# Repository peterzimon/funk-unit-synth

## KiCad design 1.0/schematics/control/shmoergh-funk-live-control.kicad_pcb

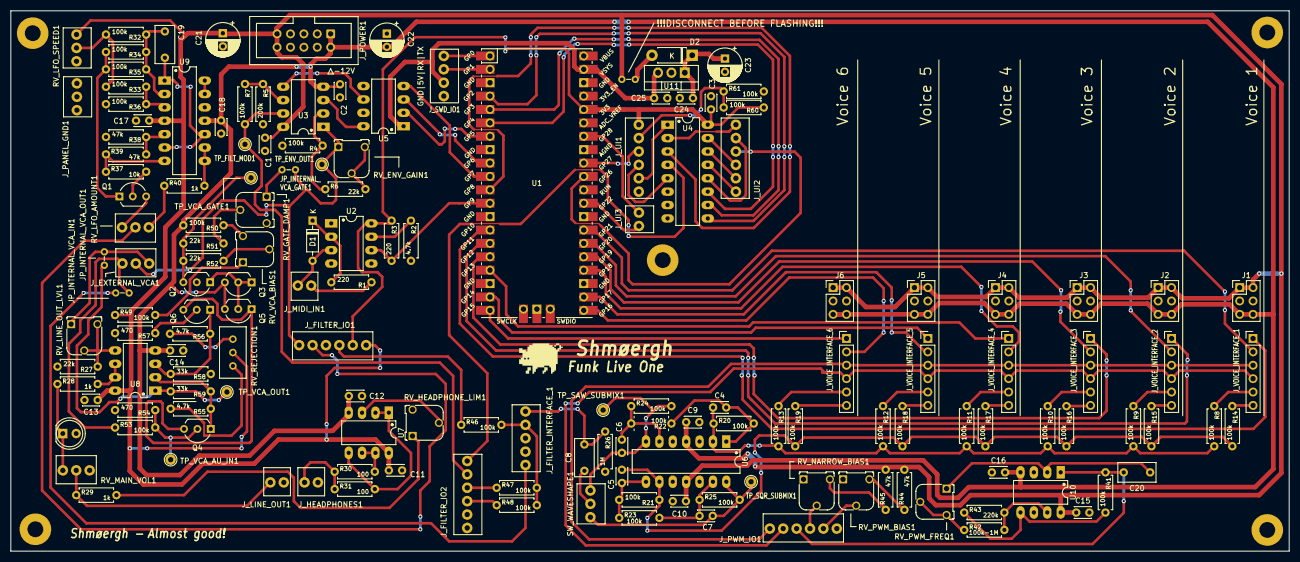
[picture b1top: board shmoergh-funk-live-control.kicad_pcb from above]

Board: 2 copper layers, 242.5 x 102.5 mm, 161 parts (0 on the bottom side), 129 nets.

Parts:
C1, C2, C3, C9, C10, C11, C12, C13, C14, C15, C16, C17, C18, C25: 100n; C_Disc_D3.0mm_W2.0mm_P2.50mm
C4, C5, C6, C7: 22p; C_Disc_D3.0mm_W2.0mm_P2.50mm
C8: 470n (foil); C_Rect_L7.0mm_W3.5mm_P5.00mm
C19: 22n-47n (foil); C_Rect_L7.0mm_W3.5mm_P5.00mm
C20: 470n foil; C_Rect_L7.0mm_W3.5mm_P5.00mm
C21, C22: 100u; CP_Radial_D6.3mm_P2.50mm
C23: 10u; CP_Radial_D6.3mm_P2.50mm
C24: 330n; C_Disc_D3.0mm_W2.0mm_P2.50mm
D1: 1N4148; D_DO-35_SOD27_P7.62mm_Horizontal
D2: 1N4001; D_DO-41_SOD81_P7.62mm_Horizontal
D_NEGATIVE_LIMITER1: Red LED; LED_D5.0mm
H1, H2, H3, H4, H5: MountingHole; MountingHole_3mm_Pad
J1, J2, J3, J4, J5, J6: Power; PinHeader_2x03_P2.54mm_Vertical
JP_INTERNAL_VCA_GATE1: jmpr; Jumper_P2.54mm_D0.7mm
JP_INTERNAL_VCA_IN1: jmpr; Jumper_P2.54mm_D0.7mm
JP_INTERNAL_VCA_OUT1: jmpr; Jumper_P2.54mm_D0.7mm
JP_MCU_EXT_PWR2: jmpr; Jumper_P2.54mm_D0.7mm
J_EXTERNAL_VCA1: Conn_01x03; NSL25_01x03_Vertical
J_FILTER_INTERFACE_1: Conn_01x05; NSL25_01x05_Vertical
J_FILTER_IO1, J_FILTER_IO2: Conn_01x06; NSL25_01x06_Vertical
J_HEADPHONES1: 3.5mm jack; NSL25_01x02_Vertical-AudioJack-TS
J_LINE_OUT1: 3.5mm jack; NSL25_01x02_Vertical-AudioJack-TS
J_MIDI_IN1: Conn_01x02; NSL25_01x02_Vertical
J_PANEL_GND1: Conn_01x03_Pin; NSL25_01x03_Vertical
J_POWER1: Euro Power; IDC-Header_2x05_P2.54mm_Vertical
J_PWM_IO1: Conn_01x06; NSL25_01x06_Vertical
J_SWD_IO1: Conn_01x04; NSL25_01x04_Vertical
J_UI1, J_UI2: Conn_01x06; NSL25_01x06_Vertical
J_UI3: Conn_01x02; NSL25_01x02_Vertical
J_VOICE_INTERFACE_1, J_VOICE_INTERFACE_2, J_VOICE_INTERFACE_3, J_VOICE_INTERFACE_4, J_VOICE_INTERFACE_5, J_VOICE_INTERFACE_6: Conn_01x06; PinHeader_1x06_P2.54mm_Vertical
Q1: BC548C; TO-92_Inline_Wide
Q2: BC558; TO-92_Inline_Wide
Q3, Q4, Q5, Q6: BC548; TO-92_Inline_Wide
R1, R3: 220; R_Axial_DIN0207_L6.3mm_D2.5mm_P7.62mm_Horizontal
R2, R55, R56: 4.7k; R_Axial_DIN0207_L6.3mm_D2.5mm_P7.62mm_Horizontal
R4, R7, R8, R9, R10, R11, R12, R13, R14, R15, R16, R17, R18, R19, R20, R21, R22, R23, R24, R25, R32, R33, R34, R35, R36, R41, R46, R47, R48, R49, R50, R53, R60, R61: 100k; R_Axial_DIN0207_L6.3mm_D2.5mm_P7.62mm_Horizontal
R5: 200k; R_Axial_DIN0207_L6.3mm_D2.5mm_P7.62mm_Horizontal
R6, R27, R51, R52: 22k; R_Axial_DIN0207_L6.3mm_D2.5mm_P7.62mm_Horizontal
R26: 1M; R_Axial_DIN0207_L6.3mm_D2.5mm_P7.62mm_Horizontal
R28, R29, R40: 1k; R_Axial_DIN0207_L6.3mm_D2.5mm_P7.62mm_Horizontal
R30, R31: 100; R_Axial_DIN0207_L6.3mm_D2.5mm_P7.62mm_Horizontal
R37: 10k; R_Axial_DIN0207_L6.3mm_D2.5mm_P7.62mm_Horizontal
R38, R39, R44, R45: 47k; R_Axial_DIN0207_L6.3mm_D2.5mm_P7.62mm_Horizontal
R42: 100k-1M; R_Axial_DIN0207_L6.3mm_D2.5mm_P7.62mm_Horizontal
R43: 220k; R_Axial_DIN0207_L6.3mm_D2.5mm_P7.62mm_Horizontal
R54, R57: 470; R_Axial_DIN0207_L6.3mm_D2.5mm_P7.62mm_Horizontal
R58, R59: 33k; R_Axial_DIN0207_L6.3mm_D2.5mm_P7.62mm_Horizontal
RV_ENV_GAIN1: 200k; Potentiometer_Runtron_RM-065_Vertical
RV_GATE_DAMP1: 100k; Potentiometer_Runtron_RM-065_Vertical
RV_HEADPHONE_LIM1: 10k; Potentiometer_Runtron_RM-065_Vertical
RV_LFO_AMOUNT1: 100k; NSL25_01x03_Vertical
RV_LFO_SPEED1: 100k; NSL25_01x03_Vertical
RV_LINE_OUT_LVL1: 100k; Potentiometer_Runtron_RM-065_Vertical
RV_MAIN_VOL1: A100k; NSL25_01x03_Vertical
RV_NARROW_BIAS1: 100k; Potentiometer_Runtron_RM-065_Vertical
RV_PWM_BIAS1: 100k; Potentiometer_Runtron_RM-065_Vertical
RV_PWM_FREQ1: 1M; Potentiometer_Runtron_RM-065_Vertical
RV_REJECTION1: 10k; Potentiometer_Bourns_3296W_Vertical
RV_VCA_BIAS1: 100k; Potentiometer_Runtron_RM-065_Vertical
SW_WAVESHAPE1: SW_SPDT; NSL25_01x03_Vertical
TP_ENV_OUT1: TestPoint; TestPoint_THTPad_D2.0mm_Drill1.0mm
TP_FILT_MOD1: TestPoint; TestPoint_THTPad_D2.0mm_Drill1.0mm
TP_SAW_SUBMIX1: TestPoint; TestPoint_THTPad_D2.0mm_Drill1.0mm
TP_SQR_SUBMIX1: TestPoint; TestPoint_THTPad_D2.0mm_Drill1.0mm
TP_VCA_AU_IN1: TestPoint; TestPoint_THTPad_D2.0mm_Drill1.0mm
TP_VCA_GATE1: TestPoint; TestPoint_THTPad_D2.0mm_Drill1.0mm
TP_VCA_OUT1: TestPoint; TestPoint_THTPad_D2.0mm_Drill1.0mm
U1: Pico; RPi_Pico_SMD_TH
U2: 6N138; DIP-8_W7.62mm_LongPads
U3, U8, U10: TL072; DIP-8_W7.62mm_LongPads
U4: CD4051B; DIP-16_W7.62mm_LongPads
U5: MCP4822; DIP-8_W7.62mm_LongPads
U6, U9: TL074; DIP-14_W7.62mm_LongPads
U7: NE5532; DIP-8_W7.62mm_LongPads
U11: L7805; TO-220-3_Vertical

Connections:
1.5V: J_UI1.2, R60.2, R61.1
+3.3V: C3.1, J_FILTER_IO1.2, J_UI1.1, R3.1, R60.1, U1.36 (3V3), U2.8 (VCC), U4.16 (VDD)
+5V: C25.1, J_SWD_IO1.3, U1.39 (VSYS), U5.1 (Vdd), U11.3 (OUT)
+12V: C1.1, C9.1, C11.1, C13.1, C15.1, C17.1, C21.1, J1.1, J1.2, J2.1, J2.2, J3.1, J3.2, J4.1, J4.2, J5.1, J5.2, J6.1, J6.2, JP_MCU_EXT_PWR2.1 (A), J_FILTER_IO1.1, J_POWER1.9, J_POWER1.10, R44.2, R45.2, R49.1, RV_LFO_SPEED1.1, RV_REJECTION1.2, U3.8 (V+), U6.4 (V+), U7.8 (V+), U8.8 (V+), U9.4 (V+), U10.8 (V+)
-12V: C2.2, C10.2, C12.2, C14.2, C16.2, C18.2, C22.2, J1.5, J1.6, J2.5, J2.6, J3.5, J3.6, J4.5, J4.6, J5.5, J5.6, J6.5, J6.6, J_POWER1.1, J_POWER1.2, Q3.3 (E), Q5.3 (E), R50.2, U3.4 (V-), U6.11 (V-), U7.4 (V-), U8.4 (V-), U9.11 (V-), U10.4 (V-)
/Digital/AMP_1: J_VOICE_INTERFACE_1.2, U1.27 (GPIO21)
/Digital/AMP_2: J_VOICE_INTERFACE_2.2, U1.26 (GPIO20)
/Digital/AMP_3: J_VOICE_INTERFACE_3.2, U1.25 (GPIO19)
/Digital/AMP_4: J_VOICE_INTERFACE_4.2, U1.24 (GPIO18)
/Digital/AMP_5: J_VOICE_INTERFACE_5.2, U1.22 (GPIO17)
/Digital/AMP_6: J_VOICE_INTERFACE_6.2, U1.21 (GPIO16)
/Digital/Digital UI/DETUNE: J_UI1.5, U4.1 (X4)
/Digital/Digital UI/EXTRA_GPIO1: J_UI3.1, U1.34 (GPIO28_ADC2)
/Digital/Digital UI/EXTRA_GPIO2: J_UI3.2, U1.29 (GPIO22)
/Digital/Digital UI/HOLD: J_UI2.2, U4.14 (X1)
/Digital/Digital UI/KB_TRACKING: J_UI2.6, U4.2 (X6)
/Digital/Digital UI/MODE: J_UI1.3, U1.32 (GPIO27_ADC1)
/Digital/Digital UI/PORTAMENTO: J_UI2.5, U4.12 (X3)
/Digital/Digital UI/RING: J_UI2.3, U4.15 (X2)
/Digital/Digital UI/RING_TIME: J_UI2.4, U1.31 (GPIO26_ADC0)
/Digital/Digital UI/SOFT: J_UI2.1, U4.13 (X0)
/Digital/Digital UI/SOLO_CHORD: J_UI1.4, U4.5 (X5)
/Digital/ENVELOPE: JP_INTERNAL_VCA_GATE1.2 (B), J_EXTERNAL_VCA1.2, J_FILTER_IO1.6, RV_ENV_GAIN1.1, TP_ENV_OUT1.1, U3.1
/Digital/FILTER_MOD: J_FILTER_IO2.2, R7.2, TP_FILT_MOD1.1, U3.7
/Digital/RESET_1: J_VOICE_INTERFACE_1.1, U1.14 (GPIO10)
/Digital/RESET_2: J_VOICE_INTERFACE_2.1, U1.15 (GPIO11)
/Digital/RESET_3: J_VOICE_INTERFACE_3.1, U1.16 (GPIO12)
/Digital/RESET_4: J_VOICE_INTERFACE_4.1, U1.17 (GPIO13)
/Digital/RESET_5: J_VOICE_INTERFACE_5.1, U1.19 (GPIO14)
/Digital/RESET_6: J_VOICE_INTERFACE_6.1, U1.20 (GPIO15)
/Digital/WAH_VELOCITY: J_FILTER_IO2.1, U4.4 (X7)
/Filter Interface/AUDIO_IN: C8.2, J_FILTER_INTERFACE_1.1, R26.1
/Filter Interface/AUDIO_OUT: JP_INTERNAL_VCA_IN1.2 (B), J_FILTER_INTERFACE_1.5
/Filter Interface/LFO_IN: J_FILTER_IO1.5, RV_LFO_AMOUNT1.2
/LFO + PWM/PULSE_WIDTH: J_PWM_IO1.1, J_VOICE_INTERFACE_1.3, J_VOICE_INTERFACE_2.3, J_VOICE_INTERFACE_3.3, J_VOICE_INTERFACE_4.3, J_VOICE_INTERFACE_5.3, J_VOICE_INTERFACE_6.3
/LFO + PWM/PWM_OUT: J_PWM_IO1.2, J_VOICE_INTERFACE_1.4, J_VOICE_INTERFACE_2.4, J_VOICE_INTERFACE_3.4, J_VOICE_INTERFACE_4.4, J_VOICE_INTERFACE_5.4, J_VOICE_INTERFACE_6.4
/Mixer/SAW_1_IN: J_VOICE_INTERFACE_1.5, R8.1
/Mixer/SAW_2_IN: J_VOICE_INTERFACE_2.5, R9.1
/Mixer/SAW_3_IN: J_VOICE_INTERFACE_3.5, R10.1
/Mixer/SAW_4_IN: J_VOICE_INTERFACE_4.5, R11.1
/Mixer/SAW_5_IN: J_VOICE_INTERFACE_5.5, R12.1
/Mixer/SAW_6_IN: J_VOICE_INTERFACE_6.5, R13.1
/Mixer/SQR_1_IN: J_VOICE_INTERFACE_1.6, R14.1
/Mixer/SQR_2_IN: J_VOICE_INTERFACE_2.6, R15.1
/Mixer/SQR_3_IN: J_VOICE_INTERFACE_3.6, R16.1
/Mixer/SQR_4_IN: J_VOICE_INTERFACE_4.6, R17.1
/Mixer/SQR_5_IN: J_VOICE_INTERFACE_5.6, R18.1
/Mixer/SQR_6_IN: J_VOICE_INTERFACE_6.6, R19.1
/Output/AUDIO_IN: JP_INTERNAL_VCA_OUT1.2 (B), J_EXTERNAL_VCA1.3, RV_LINE_OUT_LVL1.1
/VCA (Internal)/AUDIO_IN: JP_INTERNAL_VCA_IN1.1 (A), J_EXTERNAL_VCA1.1, R53.1
/VCA (Internal)/AUDIO_OUT: JP_INTERNAL_VCA_OUT1.1 (A), R59.2, TP_VCA_OUT1.1, U8.1
/VCA (Internal)/GATE: JP_INTERNAL_VCA_GATE1.1 (A), RV_GATE_DAMP1.1
CUTOFF_IN: J_FILTER_IO1.3, R46.1
DAC_CS: U1.7 (GPIO5), U5.2 (~CS)
DAC_SCK: U1.9 (GPIO6), U5.3 (SCK)
DAC_SDI: U1.10 (GPIO7), U5.4 (SDI)
FILTER_DIGI_MOD_IN: J_FILTER_IO2.3, R47.1
GND: C1.2, C2.1, C3.2, C9.2, C10.1, C11.2, C12.1, C13.2, C14.1, C15.2, C16.1, C17.2, C18.1, C21.2, C22.1, C23.2, C24.2, C25.2, D_NEGATIVE_LIMITER1.2 (A), J1.3, J1.4, J2.3, J2.4, J3.3, J3.4, J4.3, J4.4, J5.3, J5.4, J6.3, J6.4, J_FILTER_IO2.5, J_FILTER_IO2.6, J_HEADPHONES1.S, J_LINE_OUT1.S, J_PANEL_GND1.1, J_PANEL_GND1.2, J_PANEL_GND1.3, J_POWER1.3, J_POWER1.4, J_POWER1.5, J_POWER1.6, J_POWER1.7, J_POWER1.8, J_PWM_IO1.6, J_SWD_IO1.4, J_UI1.6, Q1.3 (E), Q2.2 (B), R2.2, R4.2, R5.2, R26.2, R27.2, R36.2, R38.2, R54.2, R57.2, R58.1, R61.2, RV_GATE_DAMP1.3, RV_HEADPHONE_LIM1.3, RV_LFO_AMOUNT1.3, RV_LFO_SPEED1.3, RV_MAIN_VOL1.3, RV_NARROW_BIAS1.1, RV_PWM_BIAS1.1, U1.3 (GND), U1.8 (GND), U1.13 (GND), U1.18 (GND), U1.23 (GND), U1.28 (GND), U1.38 (GND), U2.5 (GND), U4.6 (INH), U4.7 (VEE), U4.8 (VSS), U5.5 (~LDAC), U5.7 (Vss), U6.3 (+), U6.5 (+), U6.10 (+), U6.12 (+), U9.12 (+), U10.3 (+), U10.6 (-), U11.2 (GND)
MIDI_IN: R3.2, U1.12 (GPIO9), U2.6 (VO2)
MUX_A: U1.6 (GPIO4), U4.11 (A)
MUX_B: U1.5 (GPIO3), U4.10 (B)
MUX_BINARY: U1.11 (GPIO8), U4.3 (X)
MUX_C: U1.4 (GPIO2), U4.9 (C)
unnamed: C4.2, R20.2, R22.1, U6.1
unnamed: C5.2, R21.2, R23.1, U6.8
unnamed: D1.2 (A), J_MIDI_IN1.2, U2.3 (C2)
unnamed: D1.1 (K), R1.2, U2.2 (C1)
unnamed: D2.2 (A), JP_MCU_EXT_PWR2.2 (B)
unnamed: C23.1, C24.1, D2.1 (K), U11.1 (IN)
unnamed: D_NEGATIVE_LIMITER1.1 (K), R28.1, RV_MAIN_VOL1.1
unnamed: J_FILTER_INTERFACE_1.2, R46.2, R47.2, R48.2
unnamed: J_HEADPHONES1.T, R30.1, R31.1
unnamed: J_LINE_OUT1.T, R29.1, RV_MAIN_VOL1.2
unnamed: J_MIDI_IN1.1, R1.1
unnamed: Q1.2 (B), R37.2
unnamed: Q1.1 (C), R34.2, R35.2
unnamed: Q2.1 (C), Q3.1 (C), Q3.2 (B), Q5.2 (B)
unnamed: Q2.3 (E), R51.2, R52.2, TP_VCA_GATE1.1
unnamed: Q4.2 (B), R53.2, R54.1, TP_VCA_AU_IN1.1
unnamed: Q4.1 (C), R55.1, R59.1, U8.2 (-)
unnamed: Q4.3 (E), Q5.1 (C), Q6.3 (E)
unnamed: Q6.2 (B), R57.1
unnamed: Q6.1 (C), R56.1, R58.2, U8.3 (+)
unnamed: R6.2, RV_ENV_GAIN1.2, RV_ENV_GAIN1.3
unnamed: R29.2, RV_HEADPHONE_LIM1.1
unnamed: R32.2, R33.2, RV_LFO_SPEED1.2
unnamed: R37.1, R39.1, U9.7
unnamed: R40.1, RV_LFO_AMOUNT1.1
unnamed: R42.1, RV_PWM_FREQ1.2, RV_PWM_FREQ1.3
unnamed: R42.2, R43.2, U10.7
unnamed: R44.1, RV_PWM_BIAS1.3
unnamed: R45.1, RV_NARROW_BIAS1.3
unnamed: R49.2, RV_VCA_BIAS1.1
unnamed: R50.1, RV_VCA_BIAS1.3
unnamed: R51.1, RV_GATE_DAMP1.2
unnamed: R52.1, RV_VCA_BIAS1.2
unnamed: R55.2, RV_REJECTION1.1
unnamed: R56.2, RV_REJECTION1.3
unnamed: C6.2, R24.2, SW_WAVESHAPE1.1 (A), TP_SAW_SUBMIX1.1, U6.7
unnamed: C8.1, SW_WAVESHAPE1.2 (B)
unnamed: C7.2, R25.2, SW_WAVESHAPE1.3 (C), TP_SQR_SUBMIX1.1, U6.14
unnamed: R2.1, U2.7 (VO1)
unnamed: U3.3 (+), U5.8 (VA)
unnamed: R4.1, R6.1, U3.2 (-)
unnamed: U3.5 (+), U5.6 (VB)
unnamed: R5.1, R7.1, U3.6 (-)
unnamed: C4.1, R8.2, R9.2, R10.2, R11.2, R12.2, R13.2, R20.1, U6.2 (-)
unnamed: C6.1, R22.2, R24.1, U6.6 (-)
unnamed: C5.1, R14.2, R15.2, R16.2, R17.2, R18.2, R19.2, R21.1, U6.9 (-)
unnamed: C7.1, R23.2, R25.1, U6.13 (-)
unnamed: RV_HEADPHONE_LIM1.2, U7.3 (+)
unnamed: R31.2, U7.1, U7.2 (-), U7.5 (+)
unnamed: R30.2, U7.6 (-), U7.7
unnamed: R27.1, RV_LINE_OUT_LVL1.2, RV_LINE_OUT_LVL1.3, U8.5 (+)
unnamed: R28.2, U8.6 (-), U8.7
unnamed: R33.1, R36.1, U9.3 (+)
unnamed: C19.2, R32.1, R34.1, R35.1, U9.2 (-)
unnamed: R38.1, R39.2, U9.5 (+)
unnamed: C19.1, U9.1, U9.6 (-), U9.10 (+)
unnamed: R40.2, U9.8, U9.9 (-)
unnamed: U9.13 (-), U9.14
unnamed: C20.1, RV_PWM_FREQ1.1, U10.2 (-)
unnamed: R41.2, R43.1, U10.5 (+)
PWM_LFO: C20.2, J_PWM_IO1.3, R41.1, U10.1
PWM_LFO_BIAS: J_PWM_IO1.5, RV_PWM_BIAS1.2
PWM_NARROW_BIAS: J_PWM_IO1.4, RV_NARROW_BIAS1.2
UART_RX: J_SWD_IO1.2, U1.2 (GPIO1)
UART_TX: J_SWD_IO1.1, U1.1 (GPIO0)
WAH_AMNT_IN: J_FILTER_IO2.4, R48.1

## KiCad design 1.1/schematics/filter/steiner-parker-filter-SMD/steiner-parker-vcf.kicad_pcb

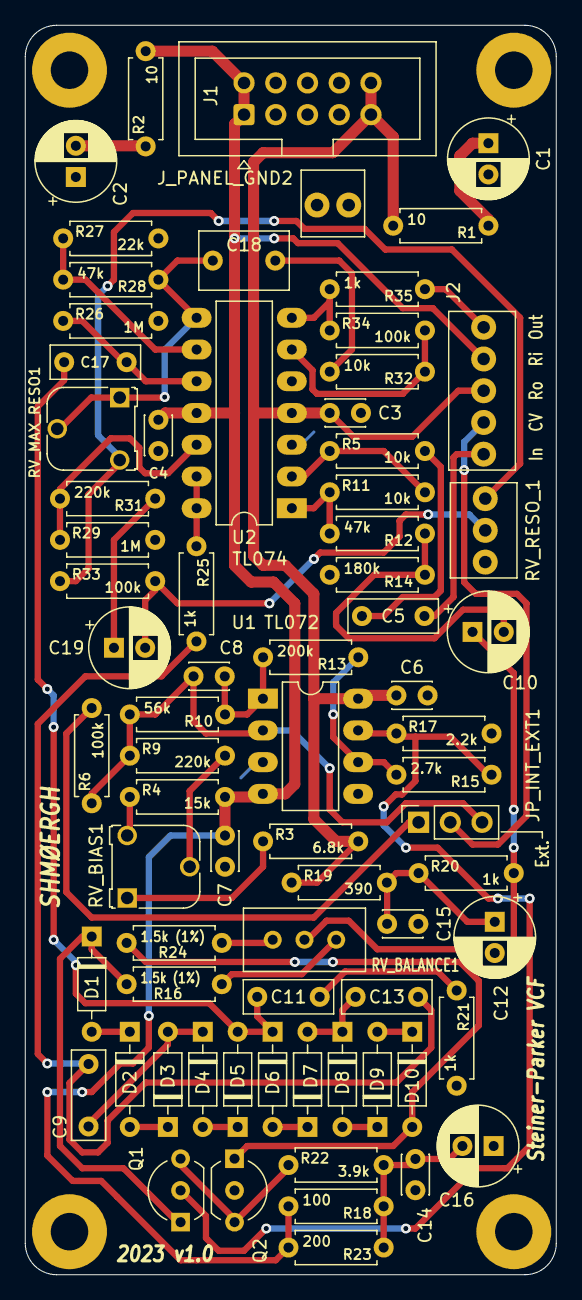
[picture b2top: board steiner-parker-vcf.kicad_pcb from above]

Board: 2 copper layers, 42.5 x 100.0 mm, 77 parts (0 on the bottom side), 50 nets.

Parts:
C1, C2, C12, C16: 100u; CP_Radial_D6.3mm_P2.50mm
C3, C4, C6, C7, C14, C15: 100n; C_Disc_D3.0mm_W2.0mm_P2.50mm
C5: 470n (Foil); C_Rect_L7.0mm_W2.5mm_P5.00mm
C8: 10n; C_Disc_D3.0mm_W2.0mm_P2.50mm
C9, C11, C13: 1n (Foil); C_Rect_L7.0mm_W2.5mm_P5.00mm
C10: 2.2u; CP_Radial_D6.3mm_P2.50mm
C17: 470n (foil); C_Rect_L7.0mm_W2.5mm_P5.00mm
C18: 1u (Foil); C_Rect_L7.0mm_W4.5mm_P5.00mm
C19: 10u; CP_Radial_D6.3mm_P2.50mm
D1, D2, D3, D4, D5, D6, D7, D8, D9, D10: 1N4148; D_DO-35_SOD27_P7.62mm_Horizontal
H1, H2, H3, H4: MountingHole; MountingHole_3mm_Pad
J1: Eurorack Power; IDC-Header_2x05_P2.54mm_Vertical
J2: Conn_01x05_Male; NSL25_01x05_Vertical
JP_INT_EXT1: Internal/External CV; PinSocket_1x03_P2.54mm_Vertical
J_PANEL_GND2: Panel ground; NSL25_01x02_Vertical
Q1, Q2: BC547B; TO-92_Inline_Wide
R1, R2: 10; R_Axial_DIN0207_L6.3mm_D2.5mm_P7.62mm_Horizontal
R3: 6.8k; R_Axial_DIN0207_L6.3mm_D2.5mm_P7.62mm_Horizontal
R4: 15k; R_Axial_DIN0207_L6.3mm_D2.5mm_P7.62mm_Horizontal
R5, R11, R32: 10k; R_Axial_DIN0207_L6.3mm_D2.5mm_P7.62mm_Horizontal
R6, R33, R34: 100k; R_Axial_DIN0207_L6.3mm_D2.5mm_P7.62mm_Horizontal
R9, R31: 220k; R_Axial_DIN0207_L6.3mm_D2.5mm_P7.62mm_Horizontal
R10: 56k; R_Axial_DIN0207_L6.3mm_D2.5mm_P7.62mm_Horizontal
R12, R28: 47k; R_Axial_DIN0207_L6.3mm_D2.5mm_P7.62mm_Horizontal
R13: 200k; R_Axial_DIN0207_L6.3mm_D2.5mm_P7.62mm_Horizontal
R14: 180k; R_Axial_DIN0207_L6.3mm_D2.5mm_P7.62mm_Horizontal
R15: 2.7k; R_Axial_DIN0207_L6.3mm_D2.5mm_P7.62mm_Horizontal
R16, R24: 1.5k (1%); R_Axial_DIN0207_L6.3mm_D2.5mm_P7.62mm_Horizontal
R17: 2.2k; R_Axial_DIN0207_L6.3mm_D2.5mm_P7.62mm_Horizontal
R18: 100; R_Axial_DIN0207_L6.3mm_D2.5mm_P7.62mm_Horizontal
R19: 390; R_Axial_DIN0207_L6.3mm_D2.5mm_P7.62mm_Horizontal
R20, R21, R25, R35: 1k; R_Axial_DIN0207_L6.3mm_D2.5mm_P7.62mm_Horizontal
R22: 3.9k; R_Axial_DIN0207_L6.3mm_D2.5mm_P7.62mm_Horizontal
R23: 200; R_Axial_DIN0207_L6.3mm_D2.5mm_P7.62mm_Horizontal
R26, R29: 1M; R_Axial_DIN0207_L6.3mm_D2.5mm_P7.62mm_Horizontal
R27: 22k; R_Axial_DIN0207_L6.3mm_D2.5mm_P7.62mm_Horizontal
RV_BALANCE1: 1k (precision); Potentiometer_Bourns_3296W_Vertical
RV_BIAS1: 10k; Potentiometer_Runtron_RM-065_Vertical
RV_MAX_RESO1: 100k; Potentiometer_Runtron_RM-065_Vertical
RV_RESO_1: 100k; NSL25_01x03_Vertical
U1: TL072; DIP-8_W7.62mm_LongPads
U2: TL074; DIP-14_W7.62mm_LongPads

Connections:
+12V: C3.1, C6.1, J1.9, J1.10, J2.3, R1.2, R3.2, R19.1, U1.8 (V+), U2.4 (V+)
-12V: C4.2, C7.2, J1.1, J1.2, J2.4, R2.2, R4.2, R18.2, R23.2, U1.4 (V-), U2.11 (V-)
AUDIO_IN: C5.2, J2.1
CV: J2.2, JP_INT_EXT1.2 (C)
GND: C1.2, C2.1, C3.2, C4.1, C6.2, C7.1, C12.2, C14.2, C15.2, C16.1, J1.3, J1.4, J1.5, J1.6, J1.7, J1.8, J_PANEL_GND2.1, J_PANEL_GND2.2, Q2.2 (B), R14.2, R17.2, R21.2, R26.2, R27.2, R29.2, RV_RESO_1.1, U1.3 (+), U1.5 (+), U2.3 (+), U2.5 (+)
unnamed: C1.1, R1.1
unnamed: C2.2, R2.1
unnamed: C5.1, R5.2
unnamed: C8.1, R10.1, R13.2, U1.1
unnamed: C10.1, R20.2, RV_BALANCE1.2
unnamed: C10.2, R12.1, R14.1
unnamed: C11.2, R21.1
unnamed: C12.1, C15.1, R19.2, R20.1
unnamed: C9.2, C13.2, R25.2
unnamed: C14.1, C16.2, R18.1, R22.2, R23.1
unnamed: C18.1, R32.2
unnamed: C18.2, R28.1, RV_MAX_RESO1.1, RV_MAX_RESO1.2, U2.8
unnamed: C19.1, R31.1
unnamed: C19.2, R33.2, RV_RESO_1.2
unnamed: D1.2 (A), D2.1 (K)
unnamed: D1.1 (K), Q1.1 (C), R16.2
unnamed: D2.2 (A), D3.1 (K)
unnamed: C9.1, D3.2 (A), D4.1 (K)
unnamed: D4.2 (A), D5.1 (K)
unnamed: C11.1, C17.2, D5.2 (A), D6.1 (K)
unnamed: D6.2 (A), D7.1 (K)
unnamed: C13.1, D7.2 (A), D8.1 (K)
unnamed: D8.2 (A), D9.1 (K)
unnamed: D10.2 (A), Q2.1 (C), R24.2
unnamed: D9.2 (A), D10.1 (K)
unnamed: JP_INT_EXT1.1 (A), R6.2
unnamed: C8.2, JP_INT_EXT1.3 (B), R6.1, R9.1, R10.2, U1.2 (-)
unnamed: Q1.2 (B), R15.1, R17.1, U1.7
unnamed: Q1.3 (E), Q2.3 (E), R22.1
unnamed: R3.1, RV_BIAS1.1
unnamed: R4.1, RV_BIAS1.3
unnamed: R9.2, RV_BIAS1.2
unnamed: R11.1, R12.2, U2.1
unnamed: R16.1, RV_BALANCE1.1
unnamed: R24.1, RV_BALANCE1.3
unnamed: R33.1, RV_MAX_RESO1.3, RV_RESO_1.3
unnamed: R34.1, R35.2, U2.7
unnamed: R13.1, R15.2, U1.6 (-)
unnamed: R5.1, R11.2, U2.2 (-)
unnamed: R32.1, R34.2, U2.6 (-)
unnamed: C17.1, R26.1, U2.10 (+)
unnamed: R27.1, R28.2, U2.9 (-)
unnamed: R29.1, R31.2, U2.12 (+)
unnamed: R25.1, U2.13 (-), U2.14
OUTPUT: J2.5, R35.1

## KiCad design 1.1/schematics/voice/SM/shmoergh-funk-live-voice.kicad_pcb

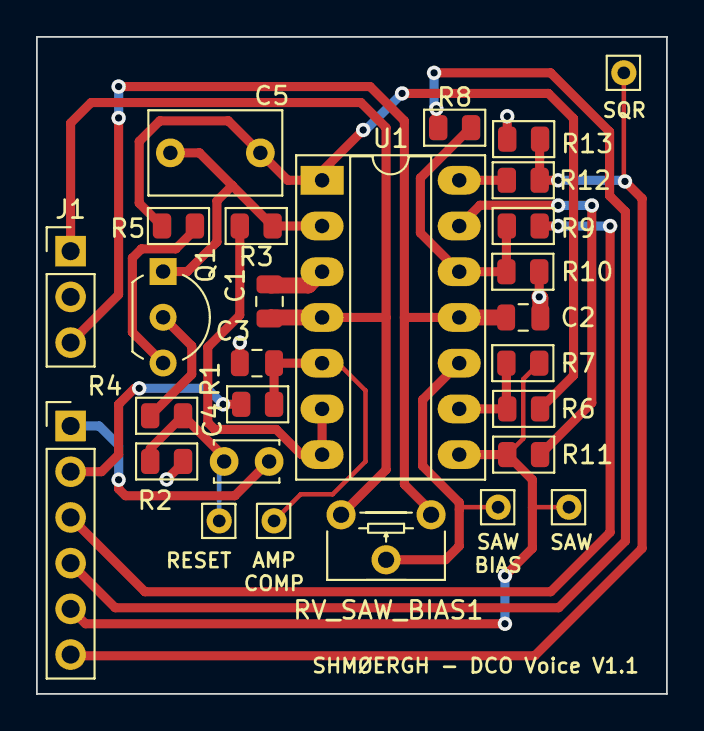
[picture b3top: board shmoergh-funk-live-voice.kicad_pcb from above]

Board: 2 copper layers, 35.0 x 36.5 mm, 28 parts (0 on the bottom side), 21 nets.

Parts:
C1, C2, C3: 100n; C_0805_2012Metric
C4: 560; C_Disc_D3.4mm_W2.1mm_P2.50mm
C5: 1n (foil); C_Rect_L7.2mm_W4.5mm_P5.00mm_FKS2_FKP2_MKS2_MKP2
J1: Power; PinHeader_1x03_P2.54mm_Vertical
J_VOICE_INTERFACE_1: Conn_01x06; PinHeader_1x06_P2.54mm_Vertical
Q1: 2N3906; TO-92L_Inline_Wide
R1: 4.7k; R_0805_2012Metric
R2, R13: 10k; R_0805_2012Metric
R3, R7: 200k; R_0805_2012Metric
R4: 1k; R_0805_2012Metric
R5: 2.2k; R_0805_2012Metric
R6, R11: 100k; R_0805_2012Metric
R8, R9: 470k; R_0805_2012Metric
R10: 330k; R_0805_2012Metric
R12: 15k; R_0805_2012Metric
RV_SAW_BIAS1: 10k fine; Potentiometer_ACP_CA6-H2,5_Horizontal
TP_AMP_COMP1: TestPoint; Pin_D0.7mm_L6.5mm_W1.8mm_FlatFork
TP_RESET1: TestPoint; Pin_D0.7mm_L6.5mm_W1.8mm_FlatFork
TP_SAW_BIAS1: TestPoint; Pin_D0.7mm_L6.5mm_W1.8mm_FlatFork
TP_SAW_OUT1: TestPoint; Pin_D0.7mm_L6.5mm_W1.8mm_FlatFork
TP_SQR_OUT1: TestPoint; Pin_D0.7mm_L6.5mm_W1.8mm_FlatFork
U1: TL074; DIP-14_W7.62mm_Socket_LongPads

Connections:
+12V: C1.1, J1.1, RV_SAW_BIAS1.3, U1.4 (V+)
-12V: C2.2, J1.3, RV_SAW_BIAS1.1, U1.11 (V-)
AMP: J_VOICE_INTERFACE_1.2, R1.2
GND: C1.2, C2.1, C3.2, J1.2, R2.2, R10.2, R13.2, U1.3 (+)
unnamed: C4.1, R2.1, R4.2, TP_RESET1.1
unnamed: C5.1, R5.2, R6.1, U1.1
unnamed: Q1.2 (B), R4.1
unnamed: Q1.3 (C), R5.1
unnamed: C5.2, Q1.1 (E), R3.1, U1.2 (-)
unnamed: R12.2, U1.14
unnamed: C3.1, R1.1, TP_AMP_COMP1.1, U1.5 (+)
unnamed: R3.2, U1.6 (-), U1.7
unnamed: RV_SAW_BIAS1.2, TP_SAW_BIAS1.1, U1.10 (+)
unnamed: R6.2, R7.1, U1.9 (-)
unnamed: R8.2, R9.2, R10.1, U1.12 (+)
unnamed: R11.1, U1.13 (-)
PULSE_WIDTH: J_VOICE_INTERFACE_1.3, R9.1
PWM: J_VOICE_INTERFACE_1.4, R8.1
RESET: C4.2, J_VOICE_INTERFACE_1.1
SAW_OUT: J_VOICE_INTERFACE_1.5, R7.2, R11.2, TP_SAW_OUT1.1, U1.8
SQR_OUT: J_VOICE_INTERFACE_1.6, R12.1, R13.1, TP_SQR_OUT1.1
